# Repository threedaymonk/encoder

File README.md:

# Encoder board with debouncing

This follows the physical dimensions of the common KY-040 type switched encoder
boards, but adds [hardware
debouncing](https://github.com/probonopd/MiniDexed/discussions/178) to allow
simpler software interfacing.

All SMT components are 0603 (Imperial). Resistors are 10kΩ, capacitors are
10nF.

Not yet tested! Use at your own risk (but let me know how it goes).

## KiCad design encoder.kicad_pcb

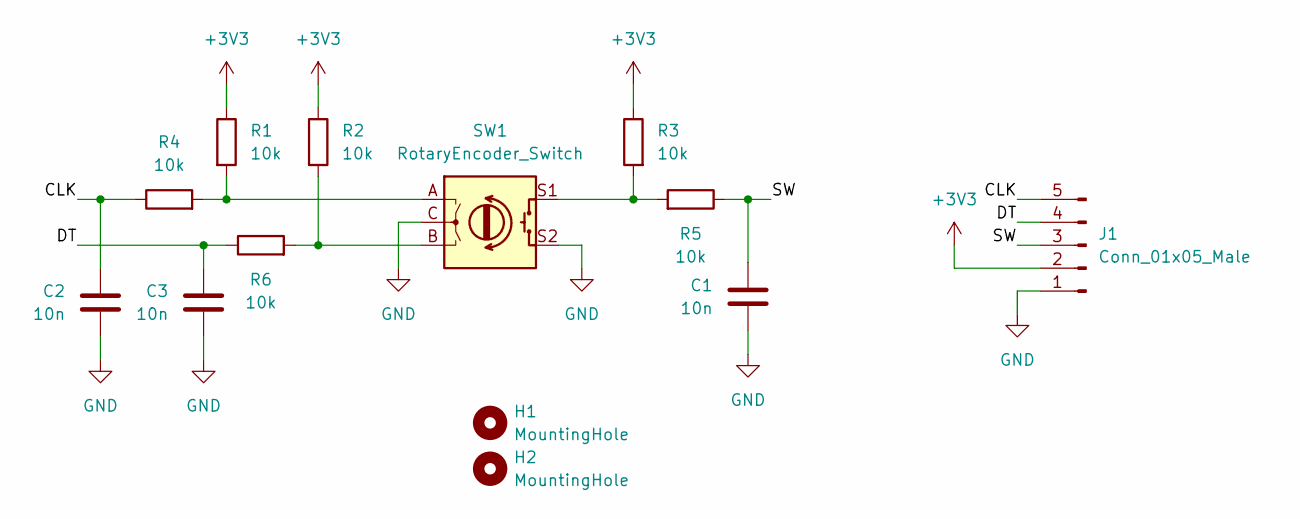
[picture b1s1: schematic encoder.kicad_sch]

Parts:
C1, C2, C3: 10n; C_0603_1608Metric_Pad1.08x0.95mm_HandSolder
H1, H2: MountingHole; MountingHole_2.7mm_M2.5
J1: Conn_01x05_Male; PinHeader_1x05_P2.54mm_Vertical
R1, R2, R3, R4, R5, R6: 10k; R_0603_1608Metric_Pad0.98x0.95mm_HandSolder
SW1: RotaryEncoder_Switch; RotaryEncoder_Alps_EC12E-Switch_Vertical_H20mm

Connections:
+3V3: J1.2, R1.1, R2.1, R3.1
/CLK: C2.2, J1.5, R4.1
/DT: C3.1, J1.4, R6.1
/SW: C1.1, J1.3, R5.1
GND: C1.2, C2.1, C3.2, J1.1, SW1.C, SW1.S2
unnamed: R1.2, R4.2, SW1.A
unnamed: R2.2, R6.2, SW1.B
unnamed: R3.2, R5.2, SW1.S1

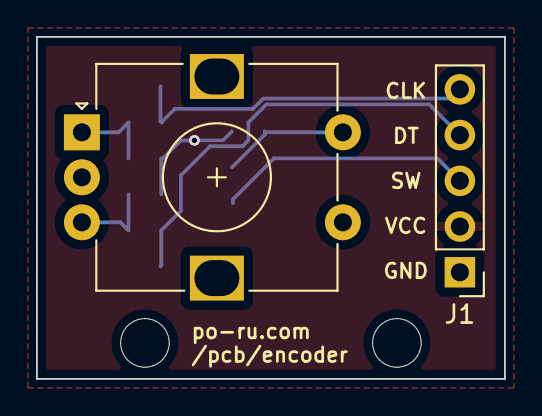
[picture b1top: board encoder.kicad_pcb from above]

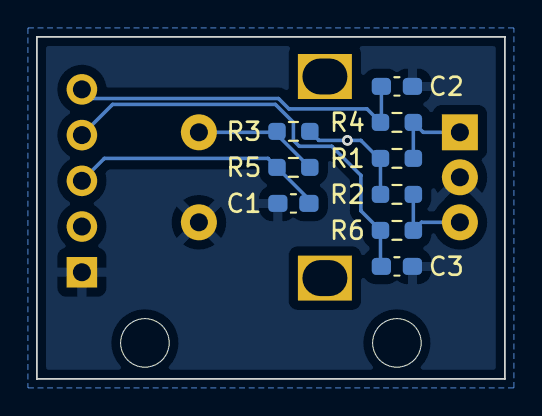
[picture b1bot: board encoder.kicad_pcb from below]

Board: 2 copper layers, 26.0 x 19.0 mm, 13 parts (9 on the bottom side), 8 nets.

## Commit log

2022-11-01 Lay out board
2022-11-01 Ignore JLC files
2022-11-01 Add documentation
2022-11-01 Add component values to README
